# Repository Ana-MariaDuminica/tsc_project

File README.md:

# TSC-Project

## BOM (Bill Of Materials)

| Component       | Supplier Link                          | Datasheet                                 |
|-----------------|----------------------------------------|-------------------------------------------|
| 112A-TAAR-R03   | [Model](https://store.comet.srl.ro/Catalogue/Product/43497/)       | [Datasheet](https://www.snapeda.com/parts/112A-TAAR-R03/Attend/datashee)|
| 744043680       | [Model](https://ro.mouser.com/ProductDetail/Wurth-Elektronik/744043680?qs=PGXP4M47uW6VkZq%252BkzjrHA%3D%3D)       | [Datasheet](https://www.we-online.com/components/products/datasheet/744043680.pdf)     |
| BD5229G-TR      | [Model](https://componentsearchengine.com/part-view/BD5229G-TR/ROHM%20Semiconductor)       | [Datasheet](https://fscdn.rohm.com/en/products/databook/datasheet/ic/power/voltage_detector/bd52xxg-e.pdf)      |
| Capacitor 0402  | [Model](https://ro.mouser.com/c/passive-components/capacitors/ceramic-capacitors/?q=CC0402&srsltid=AfmBOoogjqwwed3xvp6V5-bfVkRuawirfMcnAC47L-UQdC3mnXJk097M)       | [Datasheet](https://componentsearchengine.com/Datasheets/2/CC0402MRX5R5BB106.pdf)      |
| CPH3225A        | [Model](https://www.snapeda.com/parts/CPH3225A/Seiko+Instruments/view-part/?ref=snap)     | [Datasheet](https://www.snapeda.com/parts/CPH3225A/Seiko%20Instruments/datasheet/)      |
| Custom Button   | [Model](https://industry.panasonic.com/global/en/products/control/switch/light-touch/number/evqpuj02k)       | [Datasheet](https://industry.panasonic.com/global/en/downloads?tab=catalog&small_g_cd=203&part_no=EVQPUJ02K)      |
| DS3231SN        | [Model](https://www.snapeda.com/parts/DS3231SN%23/Analog+Devices/view-part/?ref=eda)       | [Datasheet](https://www.snapeda.com/parts/DS3231SN%23/Analog%20Devices/datasheet/)      |
| ESP32 WROVER 0805 Capacitor      | [Model](https://github.com/anaobreja/TSC-Project/blob/main)                | [Datasheet](https://github.com/anaobreja/TSC-Project/blob/main)              |
| ESP32 WROVER BME680 Sensor       | [Model](https://www.snapeda.com/parts/BME680/Bosch/view-part/?welcome=home)                | [Datasheet](https://www.bosch-sensortec.com/media/boschsensortec/downloads/datasheets/bst-bme680-ds001.pdf)              |
| ESP32 WROVER MCP73831 Power Management | [Model](https://www.snapeda.com/parts/BME680/Bosch/view-part/?welcome=home)          | [Datasheet](https://www.snapeda.com/parts/MCP73831T-2ACI/OT/Microchip/datasheet/)              |
| ESP32C6 Varistor 1812            | [Model](https://github.com/anaobreja/TSC-Project/blob/main)                | [Datasheet](https://github.com/anaobreja/TSC-Project/blob/main)              |
| ESP32C6 WROOM-1-N8               | [Model](https://www.snapeda.com/parts/ESP32-C6-WROOM-1-N8/Espressif+Systems/view-part/?ref=eda)                | [Datasheet](https://www.snapeda.com/parts/ESP32-C6-WROOM-1-N8/Espressif%20Systems/datasheet/)              |
| FH34SRJ-24S-0.5SH                | [Model](https://ro.mouser.com/ProductDetail/Hirose-Connector/FH34SRJ-24S-0.5SH99?qs=vcbW%252B4%252BSTIpKBl5ap9J8Fw%3D%3D)                | [Datasheet](https://www.snapeda.com/parts/FH34SRJ-24S-0.5SH(99)/Hirose%20Connector/datasheet/)              |
| LED Chip 0603                    | [Model](https://www.snapeda.com/parts/KP-1608SURCK/Kingbright/view-part/?ref=search&t=LED%200603)                | [Datasheet](https://www.snapeda.com/parts/KP-1608SURCK/Kingbright/datasheet/)              |
| MAX17048G+T10                    | [Model](https://www.snapeda.com/parts/MAX17048G+T10/Analog+Devices/view-part/?ref=eda)                | [Datasheet](https://www.snapeda.com/parts/MAX17048G+T10/Analog%20Devices/datasheet/)              |
| MBR0530 Schottky Diode          | [Model](https://www.snapeda.com/parts/MBR0530/Onsemi/view-part/?ref=snap)                | [Datasheet](https://www.snapeda.com/parts/MBR0530/ON%20Semiconductor/datasheet/)              |
| PGB1010603MR                     | [Model](https://www.snapeda.com/parts/PGB1010603MR/Littelfuse/view-part/?ref=eda)                | [Datasheet](https://www.snapeda.com/parts/PGB1010603MR/Littelfuse%20Inc./datasheet/)              |
| QWIIC Connector                  | [Model](https://www.snapeda.com/parts/PRT-14417/SparkFun/view-part/)                | [Datasheet](https://www.snapeda.com/parts/PRT-14417/SparkFun%20Electronics/datasheet/)              |
| RCL CPOL 3528                    | [Model](https://www.snapeda.com/parts/CPH3225A/Seiko+Instruments/view-part/?ref=eda)                | [Datasheet](https://s3.amazonaws.com/snapeda/datasheet/TAJB475K025RNJ_AVX.pdf)              |
| Resistor 0402                    | [Model](https://grabcad.com/library/resistor-0402-1)                | [Datasheet](https://www.yageo.com/upload/media/product/products/datasheet/rchip/PYu-RC_Group_51_RoHS_L_12.pdf)              |
| SI1308EDL-T1-GE3 MOSFET          | [Model](https://www.snapeda.com/parts/SI1308EDL-T1-GE3/Vishay+Siliconix/view-part/?welcome=home&ref=eda)                | [Datasheet](https://www.snapeda.com/parts/SI1308EDL-T1-GE3/Vishay%20Siliconix/datasheet/)              |
| SJ                               | [Model](https://grabcad.com/library/solder-jumpers-1)                | [Datasheet](https://github.com/anaobreja/TSC-Project/blob/main)              |
| USB4110-GF-A                     | [Model](https://componentsearchengine.com/part-view/USB4110-GF-A/GCT%20(GLOBAL%20CONNECTOR%20TECHNOLOGY))                | [Datasheet](https://gct.co/files/drawings/usb4110.pdf)              |
| USBLC6-2SC6Y                     | [Model](https://www.snapeda.com/parts/USBLC6-2SC6Y/STMicroelectronics/view-part/?welcome=home&ref=eda)                | [Datasheet](https://www.winbond.com/resource-files/W25Q512JV%20SPI%20RevB%2006252019%20KMS.pdf)              |
| W25Q512JVEIQ                     | [Model](https://www.snapeda.com/parts/W25Q512JVEIQ/Winbond+Electronics/view-part/?ref=eda)                | [Datasheet](https://www.winbond.com/resource-files/W25Q512JV%20SPI%20RevB%2006252019%20KMS.pdf)              |
| XC6220A331MR-G                   | [Model](https://componentsearchengine.com/part-view/XC6220A331MR-G/Torex)                | [Datasheet](https://product.torexsemi.com/system/files/series/xc6220.pdf)              |

## Hardware Description

**Microcontroller – ESP32-C6-WROOM-1-N8**  
The ESP32-C6 serves as the central processing unit, responsible for handling all system-level operations, communication with peripherals, and power management.  
**Architecture:** RISC-V 32-bit, **Clock Speed:** 160 MHz, **Wireless Connectivity:** 2.4 GHz Wi-Fi 6, Bluetooth 5.0  

**Power Management & Battery**  
Battery Type: Li-Po (Lithium Polymer), Capacity: 3.7V 1800mAh, Charging Circuit: MCP73831T, Input Voltage: 5V via USB-C, Protection Features: Overcharge and deep discharge protection, Voltage Regulator: LDO regulator providing 3.3V stable output  

**Display – E-Paper (E-Ink)**  
Screen Size: 7.5 inches, Resolution: 800x480 pixels, Communication Interface: SPI  

**SD Card Module**  
Type: MicroSD (supports FAT32), Interface: SPI  

**External NOR Flash**  
Capacity: 64MB, Interface: SPI  

**Environmental Sensor – BME688**  
Functions: Measures temperature, humidity, pressure, and gas levels, Communication Interface: I2C  

**Real-Time Clock (RTC) – DS3231SN**  
Functionality: Maintains time and date during power-off, Communication Interface: I2C  

**USB-C Connector & ESD Protection**  
Functionality: Provides power and data transfer, Protection: ESD protection and Schottky diode for reverse polarity  

**Buttons & User Input**  
Tactile push buttons for user interaction  

**Communication Interfaces**  
GPIO: Button control and general I/O, SPI: SD Card, NOR Flash, E-Paper Display, I2C: BME688 and DS3231SN, UART: Serial communication and debugging, Wi-Fi & Bluetooth: via ESP32-C6  

## Power Consumption Estimation
| Component                         | Current Draw (mA) | Voltage (V) | Power (mW) | Typical Current Range (mA) | Notes                            |
|----------------------------------|-------------------|-------------|------------|-----------------------------|----------------------------------|
| ESP32-C6 (Wi-Fi active)          | 140               | 3.3         | 462        | 120 – 160                   | High usage during communication |
| E-Paper Display (Updating)       | 20                | 3.3         | 66         | 15 – 26                     | Active only during refresh       |
| BME688 Sensor (Measuring)        | 2.1               | 3.3         | 6.93       | 1.7 – 3.1                   | Low-power environmental sensing |
| RTC Module (Active)              | 0.8               | 3.3         | 2.64       | 0.5 – 1                     | Minimal power requirement        |
| SD Card (Active)                 | 60                | 3.3         | 198        | 30 – 100                    | Used during data access          |
| External NOR Flash (e.g. W25Q32) | 10                | 3.3         | 33         | 4 – 20                      | Accessed for storage operations |

## ESP32-C6 Pin Mapping

| Component                         | Interface | Purpose                                                                 | ESP32-C6 Pin(s)                                         |
|----------------------------------|-----------|-------------------------------------------------------------------------|---------------------------------------------------------|
| E-Paper Display                  | SPI       | Transfers image data to the display and controls its state              | IO7 (MOSI), IO6 (SCK), IO10 (CS), IO5 (DC), IO23 (RST), IO3 (BUSY) |
| MicroSD Card                     | SPI       | Allows storage and retrieval of e-book files                            | IO7 (MOSI), IO6 (SCK), IO4 (SS_SD), IO2 (MISO)          |
| Environmental Sensor (BME688)    | I2C       | Reads temperature, humidity, pressure, and air quality data             | IO21 (SDA), IO22 (SCL)                                  |
| USB-C Connection                 | USB       | Powers and programs the ESP32-C6                                        | GPIOs through voltage regulation                        |
| Control Buttons                  | GPIO      | User input for device interactions                                      | IO9 (BOOT), IO15 (CHANGE), EN (RESET)                   |
| RTC Module (DS3231)              | I2C       | Keeps track of time even when ESP32 is off                              | IO21 (SDA), IO22 (SCL), IO18 (RST), IO1 (32KHz), IO0 (INT_RTC) |
| External NOR Flash               | SPI       | Provides additional storage for application data                        | IO11 (CS), IO6 (SCK), IO2 (MISO), IO7 (MOSI)            |
| Battery Monitoring               | I2C       | Reads battery voltage and charge status                                 | IO21 (SDA), IO22 (SCL)                                  |

## Design Notes

- The final PCB layout includes approximately **120 vias**, used primarily to optimize routing between layers while keeping signal integrity and clearance constraints in check.

- The following footprint and pad adjustments were manually made for compatibility with routing rules (specifically Copper Width DRC):

  **1. Inductor – L1 (IND_4828-WE-TPC_WRE)**  
  Footprint pad size was increased to **32mil × 16mil** to accommodate 0.3 mm (11.8mil) power traces without triggering DRC width violations.

  **2. Fuel Gauge – U4 (MAX17048G+T10, footprint SON50P200X200X80-9N)**  
  The original pad size of **29.92mil × 10.63mil** was modified to **32mil × 16mil** to ensure proper trace connection without violating clearance or minimum width rules.

- These changes ensure that all traces, especially for power delivery, comply with the netclass requirements (e.g., minimum 0.3 mm width for VBAT, VBUS, etc.) and eliminate false-positive DRC errors.

## Block Diagram

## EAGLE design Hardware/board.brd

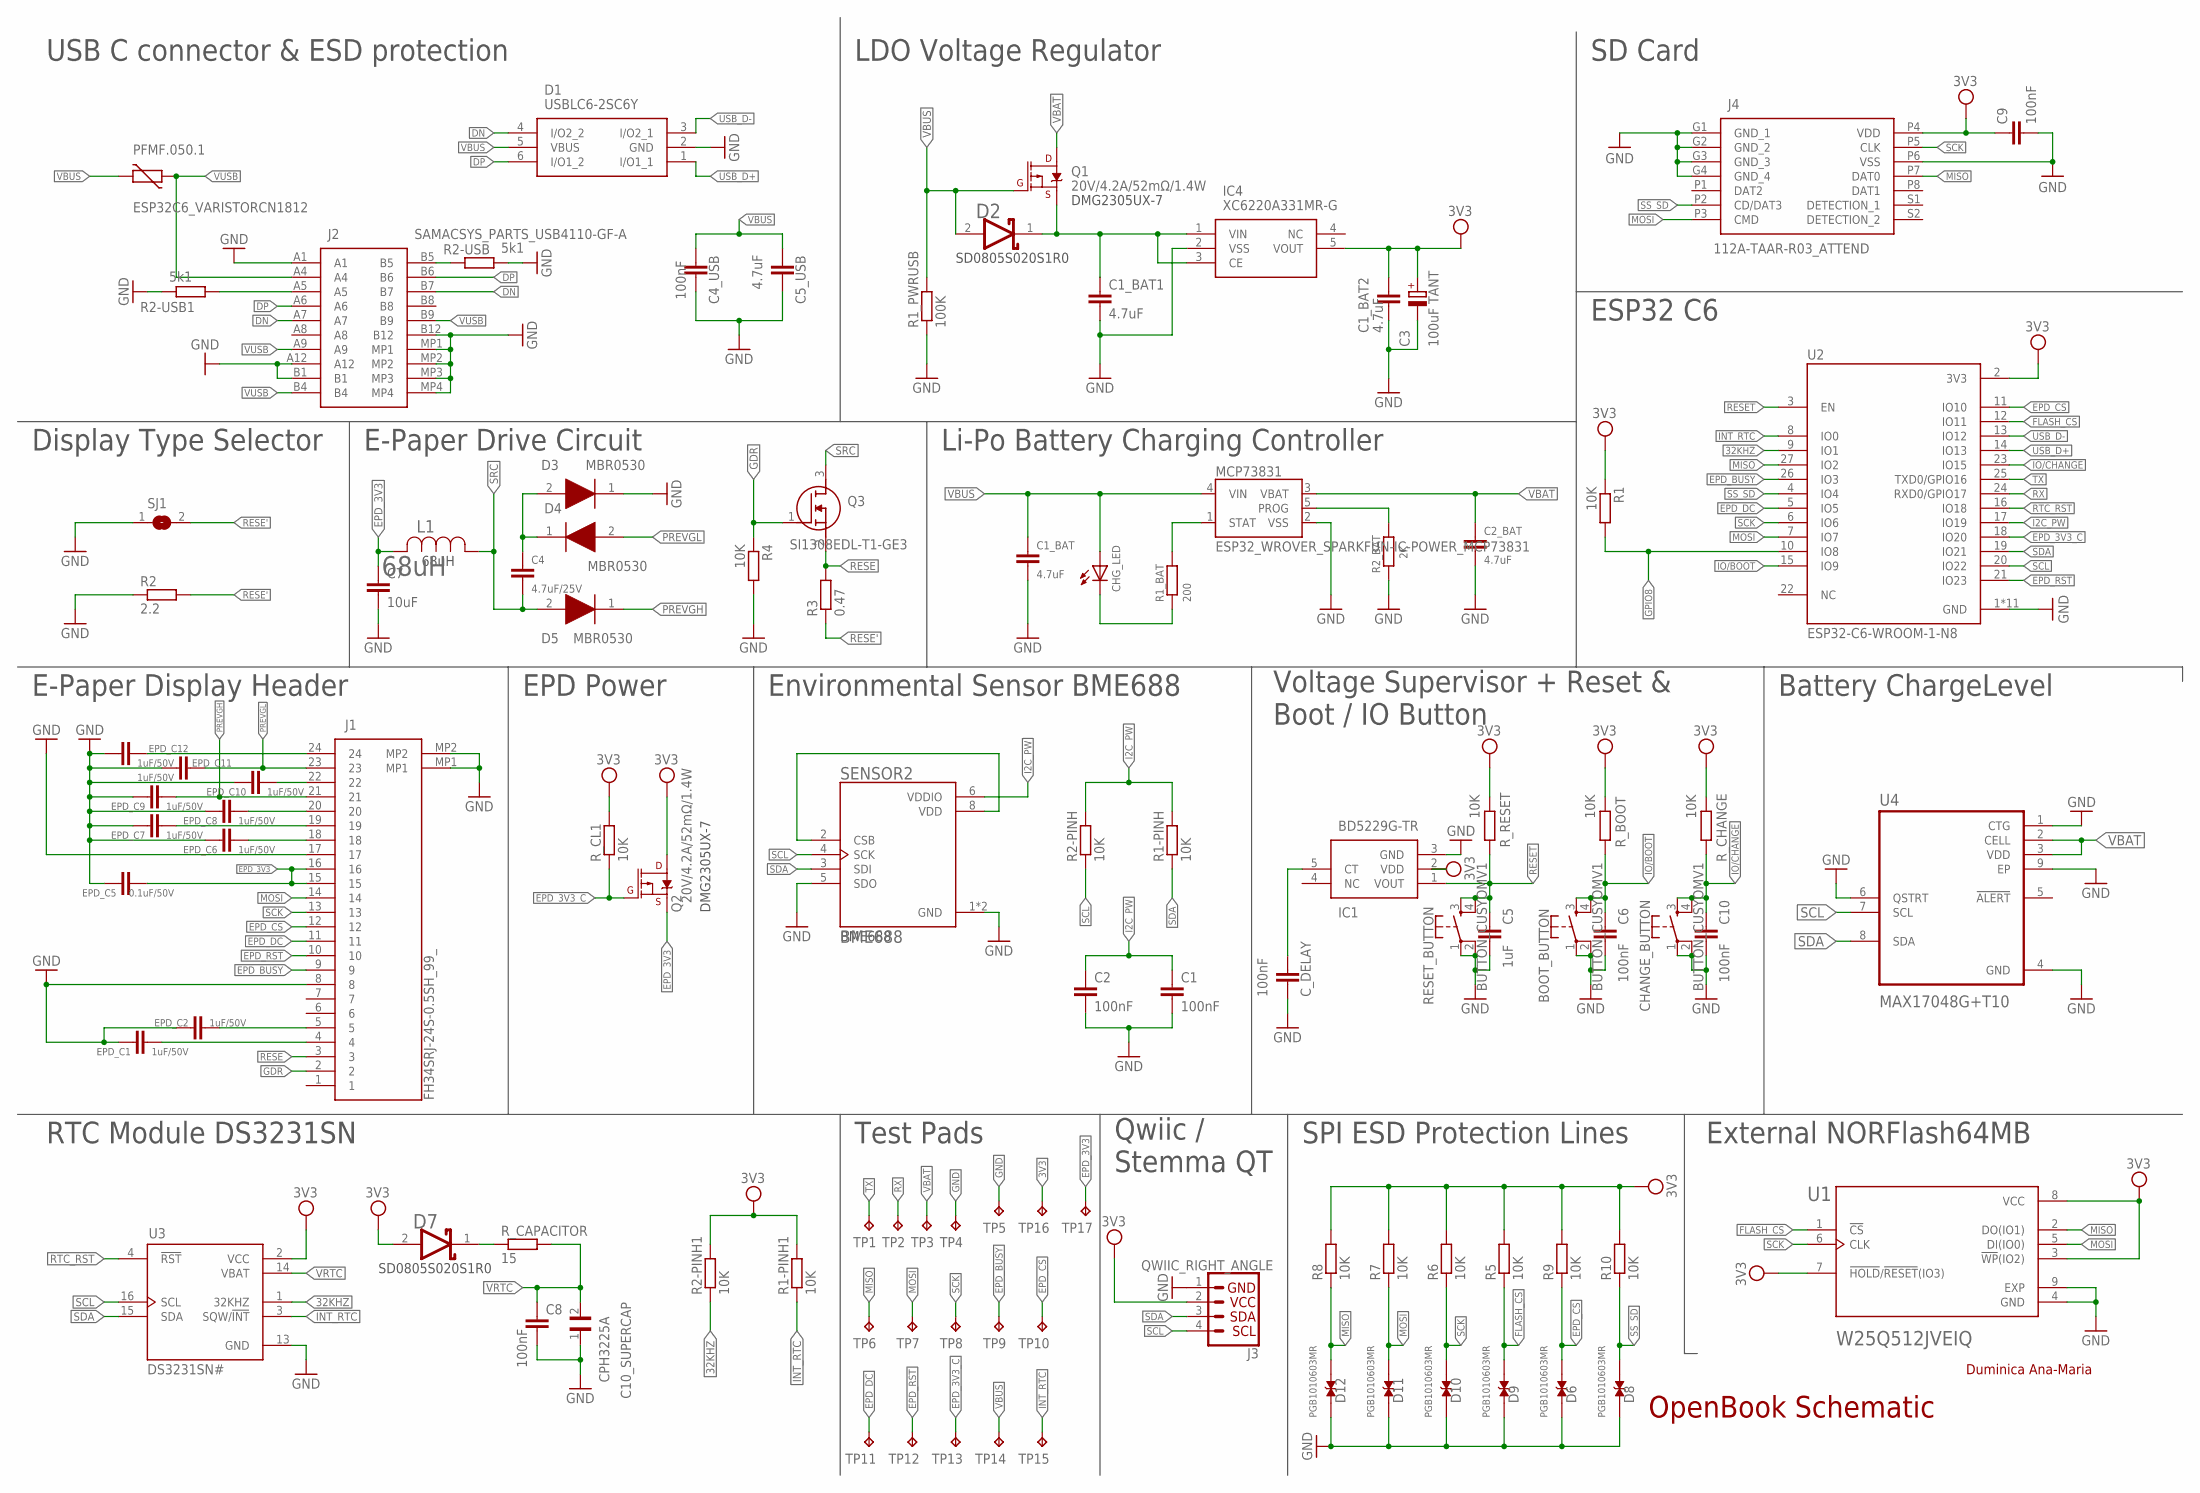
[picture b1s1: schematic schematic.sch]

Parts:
BOOT_BUTTON: BUTTON_CUSYOMV1; MYBUTTON
C1, C2, C6, C10: 100nF; ESP32_WROVER_EAGLE-LTSPICE_C0402
C1_BAT, C2_BAT: 4.7uF; ESP32_WROVER_EAGLE-LTSPICE_C0402
C1_BAT1, C1_BAT2, C5_USB: 4.7uF; EAGLE-LTSPICE_C0402
C3: 100uF TANT; RCL_CT3528
C4: 4.7uF/25V; EAGLE-LTSPICE_C0402
C4_USB, C8, C9: 100nF; EAGLE-LTSPICE_C0402
C5: 1uF; ESP32_WROVER_EAGLE-LTSPICE_C0402
C7: 10uF; EAGLE-LTSPICE_C0402
C10_SUPERCAP: CPH3225A; CAPCP3225X100N
CHANGE_BUTTON: BUTTON_CUSYOMV1; MYBUTTON
CHG_LED: ADAFRUIT_LEDCHIP-LED0603; ADAFRUIT_CHIP-LED0603
C_DELAY: 100nF; ESP32_WROVER_EAGLE-LTSPICE_C0402
D1: USBLC6-2SC6Y; SOT95P280X145-6N
D2, D7: SD0805S020S1R0; ESP32_WROVER_AVX---SD0805S020S1R0_AVX_SD0805S020S1R0_0
D3, D4, D5: MBR0530; SOD3716X135N
D6, D8, D9, D10, D11, D12: PGB1010603MR; DIOC1608X36N
EPD_C1, EPD_C2, EPD_C6, EPD_C7, EPD_C8, EPD_C9, EPD_C10, EPD_C11, EPD_C12: 1uF/50V; ESP32_WROVER_EAGLE-LTSPICE_C0402
EPD_C5: 0.1uF/50V; ESP32_WROVER_EAGLE-LTSPICE_C0402
IC1: BD5229G-TR; SOT95P280X125-5N
IC4: XC6220A331MR-G; SOT95P280X120-5N
J1: FH34SRJ-24S-0.5SH_99_; FH34SRJ24S05SH99
J2: SAMACSYS_PARTS_USB4110-GF-A; SAMACSYS_PARTS_USB4110GFA
J3: QWIIC_RIGHT_ANGLE; JST04_1MM_RA
J4: 112A-TAAR-R03_ATTEND; 112ATAARR03ATTEND
L1: 68uH; IND_4828-WE-TPC_WRE
MCP73831: ESP32_WROVER_SPARKFUN-IC-POWER_MCP73831; ESP32_WROVER_SPARKFUN-IC-POWER_SOT23-5
PFMF.050.1: ESP32C6_VARISTORCN1812; ESP32C6_VARISTOR_CT/CN1812
Q1, Q2: 20V/4.2A/52mΩ/1.4W; ESP32_WROVER_SPARKFUN-DISCRETESEMI_SOT23-3
Q3: SI1308EDL-T1-GE3; SOT65P210X110-3N
R1, R1-PINH, R1-PINH1, R2-PINH, R2-PINH1, R4, R5, R6, R7, R8, R9, R10: 10K; ESP32_WROVER_EAGLE-LTSPICE_R0402
R1_BAT: 200; ESP32_WROVER_EAGLE-LTSPICE_R0402
R1_PWRUSB: 100K; ESP32_WROVER_EAGLE-LTSPICE_R0402
R2: 2.2; ESP32_WROVER_EAGLE-LTSPICE_R0402
R2-USB, R2-USB1: 5k1; ESP32_WROVER_EAGLE-LTSPICE_R0402
R2_BAT: 2K; ESP32_WROVER_EAGLE-LTSPICE_R0402
R3: 0.47; ESP32_WROVER_EAGLE-LTSPICE_R0402
RESET_BUTTON: BUTTON_CUSYOMV1; MYBUTTON
R_BOOT: 10K; ESP32_WROVER_EAGLE-LTSPICE_R0402
R_CAPACITOR: 15; ESP32_WROVER_EAGLE-LTSPICE_R0402
R_CHANGE: 10K; ESP32_WROVER_EAGLE-LTSPICE_R0402
R_CL1: 10K; ESP32_WROVER_EAGLE-LTSPICE_R0402
R_RESET: 10K; ESP32_WROVER_EAGLE-LTSPICE_R0402
SENSOR2: BME688; ESP32_WROVER_BME680_PSON80P300X300X100-8N
SJ1: SJ
TP1, TP2, TP3, TP4, TP5, TP6, TP7, TP8, TP9, TP10, TP11, TP12, TP13, TP14, TP15, TP16, TP17: TPTP20R; TP20R
U1: W25Q512JVEIQ; SON127P600X800X80-9N
U2: ESP32-C6-WROOM-1-N8; XCVR_ESP32-C6-WROOM-1-N8
U3: DS3231SN#; SOIC127P1032X265-16N
U4: MAX17048G+T10; SON50P200X200X80-9N

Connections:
3V3: C1_BAT2.1, C3.+, C9.1, D7.2 (ANODE), IC1.2 (VDD), IC4.5 (VOUT), J3.2, J4.P4 (VDD), Q2.3 (D), R1.1, R1-PINH1.2, R2-PINH1.2, R5.2, R6.2, R7.2, R8.2, R9.2, R10.2, R_BOOT.2, R_CHANGE.2, R_CL1.2, R_RESET.2, TP16.TP, U1.3 (!WP!(IO2)), U1.7 (!HOLD!/!RESET!(IO3)), U1.8 (VCC), U2.2 (3V3), U3.2 (VCC)
32KHZ: R2-PINH1.1, U2.9 (IO1), U3.1 (32KHZ)
DN: D1.4 (I/O2_2), J2.A7, J2.B7
DP: D1.6 (I/O1_2), J2.A6, J2.B6
EPD_3V3: C7.1, EPD_C5.2, J1.15, J1.16, L1.2, Q2.2 (S), TP17.TP
EPD_3V3_C: Q2.1 (G), R_CL1.1, TP13.TP, U2.18 (IO20)
EPD_BUSY: J1.9, TP9.TP, U2.26 (IO3)
EPD_CS: D6.2, J1.12, R9.1, TP10.TP, U2.11 (IO10)
EPD_DC: J1.11, TP11.TP, U2.5 (IO5)
EPD_RST: J1.10, TP12.TP, U2.21 (IO23)
FLASH_CS: D9.2, R5.1, U1.1 (!CS), U2.12 (IO11)
GDR: J1.2, Q3.1 (G), R4.1
GND: BOOT_BUTTON.1, BOOT_BUTTON.2, C1.2, C1_BAT.2, C1_BAT1.2, C1_BAT2.2, C2.2, C2_BAT.2, C3.-, C4_USB.2, C5.2, C5_USB.2, C6.2, C7.2, C8.2, C9.2, C10.2, C10_SUPERCAP.1, CHANGE_BUTTON.1, CHANGE_BUTTON.2, C_DELAY.2, D1.2 (GND), D3.1 (K), D6.1, D8.1, D9.1, D10.1, D11.1, D12.1, EPD_C1.1, EPD_C2.1, EPD_C5.1, EPD_C6.1, EPD_C7.1, EPD_C8.1, EPD_C9.1, EPD_C10.1, EPD_C11.1, EPD_C12.1, IC1.3 (GND), IC4.2 (VSS), J1.8, J1.17, J1.MP1, J1.MP2, J2.A1, J2.A12, J2.B1, J2.B12, J2.MP1, J2.MP2, J2.MP3, J2.MP4, J3.1, J4.G1 (GND_1), J4.G2 (GND_2), J4.G3 (GND_3), J4.G4 (GND_4), J4.P6 (VSS), MCP73831.2 (VSS), R1_PWRUSB.1, R2.1, R2-USB.2, R2-USB1.1, R2_BAT.1, R4.2, RESET_BUTTON.1, RESET_BUTTON.2, SENSOR2.1 (GND), SENSOR2.5 (SDO), SENSOR2.7 (GND), SJ1.1, TP4.TP, TP5.TP, U1.4 (GND), U1.9 (EXP), U2.1 (GND), U2.28 (GND), U2.29_1 (GND), U2.29_2 (GND), U2.29_3 (GND), U2.29_4 (GND), U2.29_5 (GND), U2.29_6 (GND), U2.29_7 (GND), U2.29_8 (GND), U2.29_9 (GND), U3.13 (GND), U4.1 (CTG), U4.4 (GND), U4.6 (QSTRT), U4.9 (EP)
GPIO8: R1.2, U2.10 (IO8)
I2C_PW: C1.1, C2.1, R1-PINH.2, R2-PINH.2, SENSOR2.6 (VDDIO), U2.17 (IO19)
INT_RTC: R1-PINH1.1, TP15.TP, U2.8 (IO0), U3.3 (SQW/!INT)
IO/BOOT: BOOT_BUTTON.3, BOOT_BUTTON.4, C6.1, R_BOOT.1, U2.15 (IO9)
IO/CHANGE: C10.1, CHANGE_BUTTON.3, CHANGE_BUTTON.4, R_CHANGE.1, U2.23 (IO15)
MISO: D12.2, J4.P7 (DAT0), R8.1, TP6.TP, U1.2 (DO(IO1)), U2.27 (IO2)
MOSI: D11.2, J1.14, J4.P3 (CMD), R7.1, TP7.TP, U1.5 (DI(IO0)), U2.7 (IO7)
unnamed: J2.A5, R2-USB1.2
unnamed: C1_BAT1.1, D2.1 (CATHODE), IC4.1 (VIN), IC4.3 (CE), Q1.2 (S)
unnamed: MCP73831.1 (STAT), R1_BAT.2
unnamed: CHG_LED.C, R1_BAT.1
unnamed: J2.B5, R2-USB.1
unnamed: MCP73831.5 (PROG), R2_BAT.2
unnamed: C4.1, D3.2 (A), D4.1 (K)
unnamed: EPD_C6.2, J1.18
unnamed: C_DELAY.1, IC1.5 (CT)
unnamed: EPD_C8.2, J1.20
unnamed: EPD_C7.2, J1.19
unnamed: EPD_C1.2, J1.4
unnamed: EPD_C10.2, J1.22
unnamed: EPD_C2.2, J1.5
unnamed: EPD_C12.2, J1.24
unnamed: SENSOR2.2 (CSB), SENSOR2.8 (VDD)
unnamed: D7.1 (CATHODE), R_CAPACITOR.1
PREVGH: D5.1 (K), EPD_C9.2, J1.21
PREVGL: D4.2 (A), EPD_C11.2, J1.23
RESE: J1.3, Q3.2 (S), R3.2
RESE': R2.2, R3.1, SJ1.2
RESET: C5.1, IC1.1 (VOUT), RESET_BUTTON.3, RESET_BUTTON.4, R_RESET.1, U2.3 (EN)
RTC_RST: U2.16 (IO18), U3.4 (!RST)
RX: TP2.TP, U2.24 (RXD0/GPIO17)
SCK: D10.2, J1.13, J4.P5 (CLK), R6.1, TP8.TP, U1.6 (CLK), U2.6 (IO6)
SCL: J3.4, R2-PINH.1, SENSOR2.4 (SCK), U2.20 (IO22), U3.16 (SCL), U4.7 (SCL)
SDA: J3.3, R1-PINH.1, SENSOR2.3 (SDI), U2.19 (IO21), U3.15 (SDA), U4.8 (SDA)
SRC: C4.2, D5.2 (A), L1.1, Q3.3 (D)
SS_SD: D8.2, J4.P2 (CD/DAT3), R10.1, U2.4 (IO4)
TX: TP1.TP, U2.25 (TXD0/GPIO16)
USB_D+: D1.1 (I/O1_1), U2.14 (IO13)
USB_D-: D1.3 (I/O2_1), U2.13 (IO12)
VBAT: C2_BAT.1, MCP73831.3 (VBAT), Q1.3 (D), TP3.TP, U4.2 (CELL), U4.3 (VDD)
VBUS: C1_BAT.1, C4_USB.1, C5_USB.1, CHG_LED.A, D1.5 (VBUS), D2.2 (ANODE), MCP73831.4 (VIN), PFMF.050.1.2, Q1.1 (G), R1_PWRUSB.2, TP14.TP
VRTC: C8.1, C10_SUPERCAP.2, R_CAPACITOR.2, U3.14 (VBAT)
VUSB: J2.A4, J2.A9, J2.B4, J2.B9, PFMF.050.1.1

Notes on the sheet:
SD Card
USB C connector & ESD protection
LDO Voltage Regulator
Li-Po Battery Charging Controller
ESP32 C6
E-Paper Drive Circuit
Display Type Selector
E-Paper Display Header
EPD Power
Environmental Sensor BME688
Voltage Supervisor + Reset & Boot / IO Button
Battery ChargeLevel
RTC Module DS3231SN
Test Pads
Qwiic / Stemma QT
SPI ESD Protection Lines
External NORFlash64MB
OpenBook Schematic
DMG2305UX-7
SD0805S020S1R0
68uH
BME688
Duminica Ana-Maria

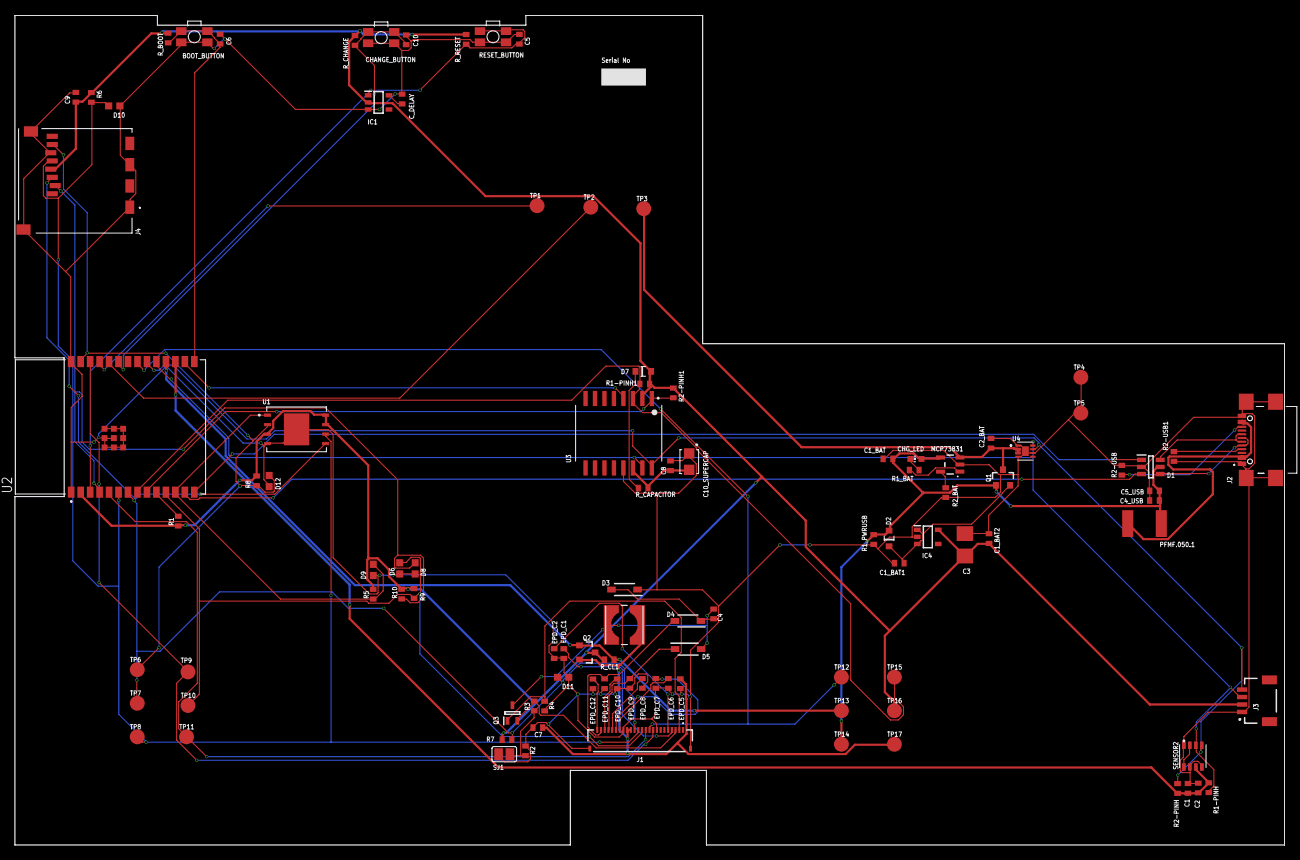
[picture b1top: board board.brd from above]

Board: 2 copper layers, 170.2 x 111.2 mm, 103 parts (0 on the bottom side), 56 nets.

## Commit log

2025-04-06 Create l
2025-04-06 Create k
2025-04-06 Create s
2025-04-06 Create g
2025-04-06 Create LICENSE
2025-04-11 Create p

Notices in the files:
parts and their libraries:
COPYRIGHT: Copyright (C) 2024 Ultra Librarian. All rights reserved.
